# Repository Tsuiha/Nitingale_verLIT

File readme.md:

Nitingale ver.LIT
30keys left hand keyboard, gaming device, macropad
rp2040 qmk keyboard

Contact
Twitter : @TsuihaJP
E-mail : contact@tsuiha.com

build guide : https://tsuiha.com/nitingale_lit_buildguide/
describe : https://tsuiha.com/nitingale_verlit/

In addition to the pcb, an M2 x 2 mm screw, an M2 x 5 mm spacer and a gateron lowprofile 2.0 switch are required

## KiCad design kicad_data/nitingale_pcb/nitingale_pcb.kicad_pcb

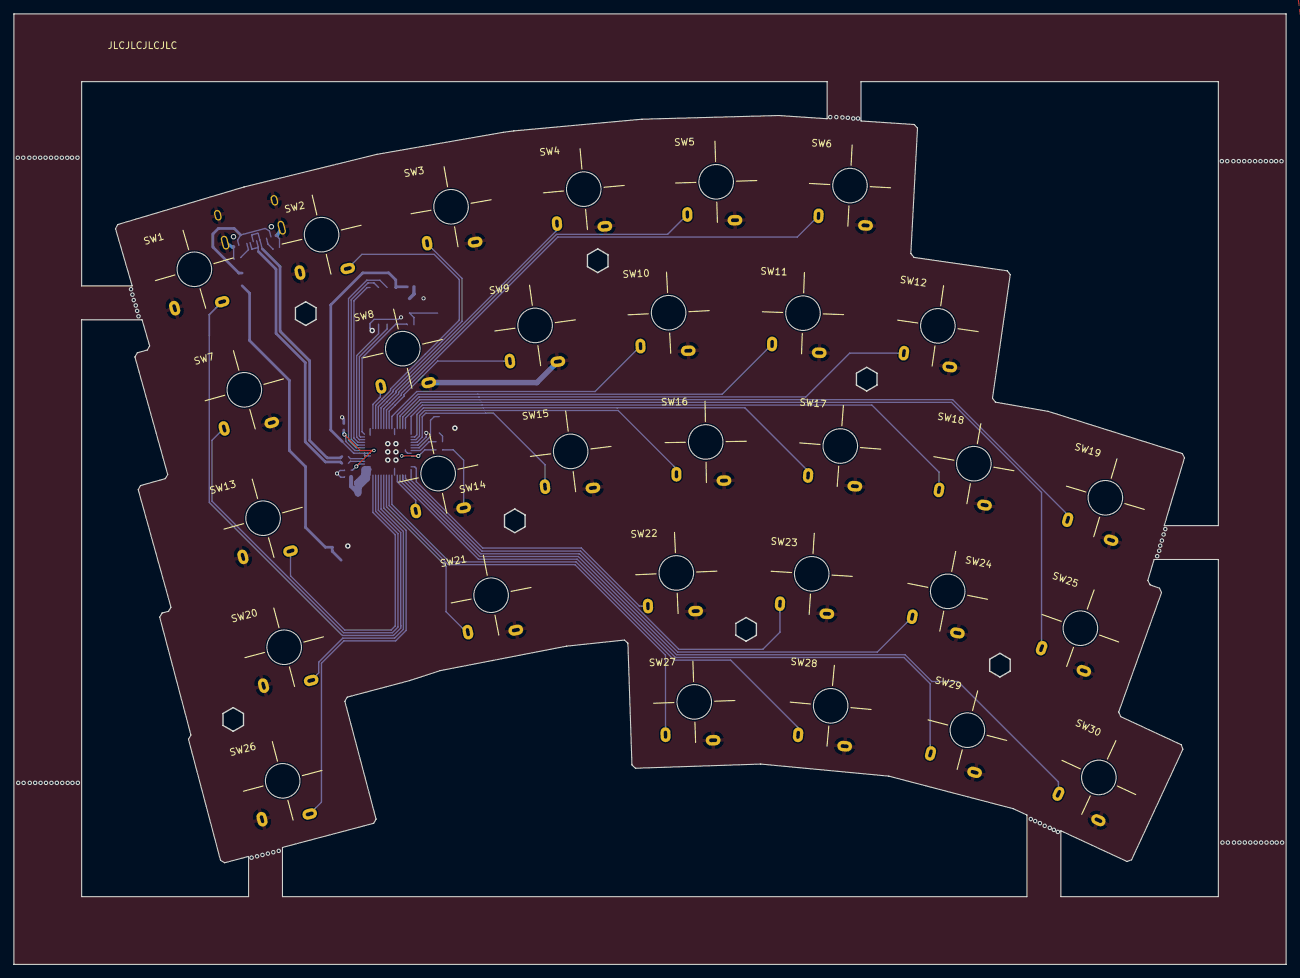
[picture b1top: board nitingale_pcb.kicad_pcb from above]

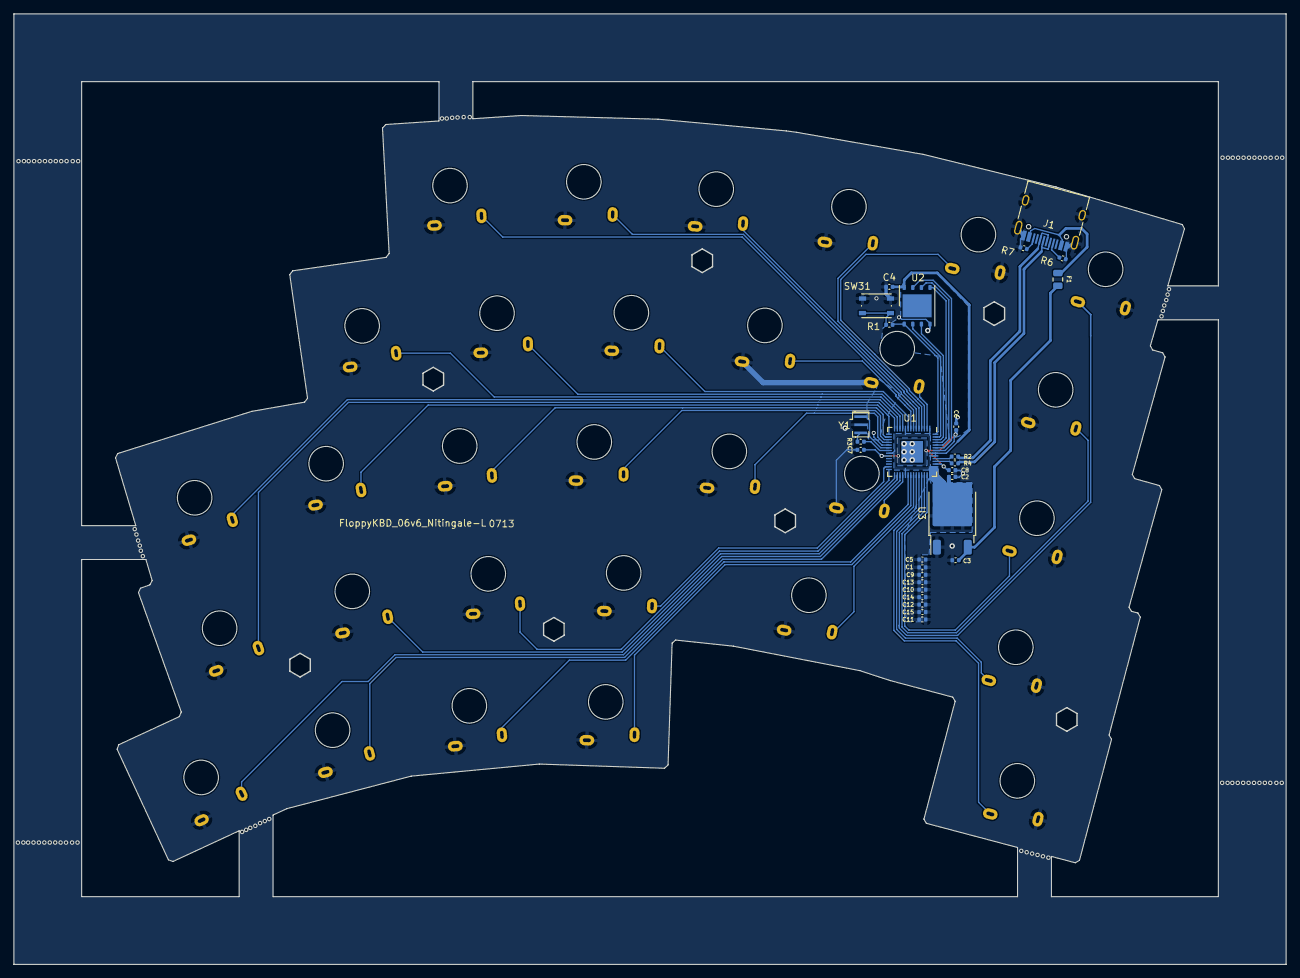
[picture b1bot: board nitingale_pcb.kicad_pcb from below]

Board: 2 copper layers, 187.7 x 140.2 mm, 58 parts (28 on the bottom side), 51 nets.

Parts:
C1, C4, C6, C7, C9, C10, C11, C12, C13, C14: 100n; C_0402_1005Metric
C2, C8: 1u; C_0402_1005Metric
C3, C5, C15: 10u; C_0402_1005Metric
F1: Polyfuse; Fuse_0805_2012Metric
J1: USB_C_Receptacle; USB_C_Receptacle_HRO_TYPE-C-31-M-12
R1, R3: 1k; C_0402_1005Metric
R2, R4: 27; C_0402_1005Metric
R6, R7: 5.1k; C_0402_1005Metric
SW1, SW2, SW3, SW4, SW5, SW6, SW7, SW8, SW9, SW10, SW11, SW12, SW13, SW14, SW15, SW16, SW17, SW18, SW19, SW20, SW21, SW22, SW23, SW24, SW25, SW26, SW27, SW28, SW29, SW30: SW_PUSH; GLP2-nitingale
SW31: SW_PUSH; SW_Push_1P1T_NO_Vertical_Wuerth_434133025816
U1: RP2040; QFN-56-1EP_7x7mm_P0.4mm_EP3.2x3.2mm
U2: W25Q128JVS; WSON-8-1EP_6x5mm_P1.27mm_EP3.4x4.3mm
U3: NCP1117-1.5_TO252; TO-252-2
Y1: Crystal_GND2; Resonator_SMD_Murata_CSTxExxV-3Pin_3.0x1.1mm

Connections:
+1V1: C6.1, C7.1, C8.1, U1.23 (DVDD), U1.45 (VREG_VOUT), U1.50 (DVDD)
+3V3: C1.1, C2.1, C4.1, C5.1, C9.1, C10.1, C11.1, C12.1, C13.1, C14.1, C15.1, U1.1 (IOVDD), U1.10 (IOVDD), U1.22 (IOVDD), U1.33 (IOVDD), U1.42 (IOVDD), U1.43 (ADC_AVDD), U1.44 (VREG_IN), U1.48 (USB_VDD), U1.49 (IOVDD), U2.8 (VCC), U3.2 (VO)
/QSPI_SCLK: U1.52 (QSPI_SCLK), U2.6 (CLK)
/QSPI_SD0: U1.53 (QSPI_SD0), U2.5 (DI(IO0))
/QSPI_SD1: U1.55 (QSPI_SD1), U2.2 (DO(IO1))
/QSPI_SD2: U1.54 (QSPI_SD2), U2.3 (IO2)
/QSPI_SD3: U1.51 (QSPI_SD3), U2.7 (IO3)
/QSPI_SS: R1.1, U1.56 (QSPI_SS), U2.1 (~CS)
/USB_D+: J1.A6 (D+), J1.B6 (D+), R2.2
/USB_D-: J1.A7 (D-), J1.B7 (D-), R4.2
/XIN: U1.20 (XIN), Y1.1
/XOUT: R3.1, U1.21 (XOUT)
/~USB_BOOT: R1.2, SW31.1
GND: C1.2, C2.2, C3.2, C4.2, C5.2, C6.2, C7.2, C8.2, C9.2, C10.2, C11.2, C12.2, C13.2, C14.2, C15.2, J1.A1 (GND), J1.A12 (GND), J1.B1 (GND), J1.B12 (GND), J1.S1 (SHIELD), R6.1, R7.1, SW1.1, SW2.1, SW3.2, SW4.2, SW5.2, SW6.2, SW7.2, SW8.2, SW9.2, SW10.2, SW11.2, SW12.2, SW13.1, SW14.2, SW15.2, SW16.2, SW17.2, SW18.2, SW19.2, SW20.1, SW21.2, SW22.2, SW23.2, SW24.2, SW25.2, SW26.1, SW27.2, SW28.2, SW29.2, SW30.2, SW31.2, U1.19 (TESTEN), U1.57 (GND), U2.4 (GND), U3.1 (GND), Y1.2
unnamed: J1.A5 (CC1), R6.2
unnamed: J1.B5 (CC2), R7.2
unnamed: R3.2, Y1.3
unnamed: R4.1, U1.46 (USB_DM)
unnamed: R2.1, U1.47 (USB_DP)
unnamed: C3.1, F1.2, U3.3 (VI)
VBUS: F1.1, J1.A4 (VBUS), J1.A9 (VBUS), J1.B4 (VBUS), J1.B9 (VBUS)
sw01: SW1.2, U1.39 (GPIO27_ADC1)
sw02: SW2.2, U1.3 (GPIO1)
sw03: SW3.1, U1.4 (GPIO2)
sw04: SW4.1, U1.5 (GPIO3)
sw05: SW5.1, U1.6 (GPIO4)
sw06: SW6.1, U1.7 (GPIO5)
sw07: SW7.1, U1.40 (GPIO28_ADC2)
sw08: SW8.1, U1.2 (GPIO0)
sw09: SW9.1, U1.8 (GPIO6)
sw10: SW10.1, U1.9 (GPIO7)
sw11: SW11.1, U1.11 (GPIO8)
sw12: SW12.1, U1.12 (GPIO9)
sw13: SW13.2, U1.41 (GPIO29_ADC3)
sw14: SW14.1, U1.32 (GPIO21)
sw15: SW15.1, U1.18 (GPIO15)
sw16: SW16.1, U1.17 (GPIO14)
sw17: SW17.1, U1.16 (GPIO13)
sw18: SW18.1, U1.15 (GPIO12)
sw19: SW19.1, U1.13 (GPIO10)
sw20: SW20.2, U1.38 (GPIO26_ADC0)
sw21: SW21.1, U1.36 (GPIO24)
sw22: SW22.1, U1.27 (GPIO16)
sw23: SW23.1, U1.28 (GPIO17)
sw24: SW24.1, U1.29 (GPIO18)
sw25: SW25.1, U1.14 (GPIO11)
sw26: SW26.2, U1.37 (GPIO25)
sw27: SW27.1, U1.35 (GPIO23)
sw28: SW28.1, U1.34 (GPIO22)
sw29: SW29.1, U1.31 (GPIO20)
sw30: SW30.1, U1.30 (GPIO19)

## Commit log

2024-03-24 upload data
